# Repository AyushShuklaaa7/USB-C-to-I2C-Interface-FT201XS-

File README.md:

Overview

This project converts USB communication to I2C using the FT201XS, making it useful for testing, debugging, or interfacing with I2C-based sensors and modules.
The board is powered via USB-C and includes an onboard LDO to generate a stable 3.3V supply, which is used for both the IC and I2C communication.

## Preview

⚙️Key Components

1. FT201XS (USB to I2C Bridge)
2. TPS7A20_03 (3.3V LDO)
3. USB-C Connector
4. Power Indicator LED

🧠 Design Approach & Working

* This board is designed to provide a simple bridge between USB and I2C communication using the FT201XS IC.
* the USB D+/D- differential pairs are routed with matched lengths and kept short to ensure error-free USB Full-Speed communication.
* When the board is connected via USB-C, the 5V (VBUS) from the USB is used as the primary power source. This 5V is passed through a polyfuse for overcurrent protection and then filtered using a ferrite bead to reduce high-frequency noise. A power indicator LED is connected to VBUS to show when the board is powered.
* The 5V input is then regulated down to 3.3V using an onboard LDO. This 3.3V supply powers the FT201XS IC,The FT201XS acts as a USB-to-I2C bridge.
* It communicates with the host computer over USB and converts those signals into I2C signals (SDA and SCL), which are exposed through the output header.
* For flexibility, both 3.3V (regulated) and 5V (VBUS) are exposed on the output header. While 5V can be used to power external modules, the I2C communication itself is strictly limited to 3.3V logic levels.
* Additional protection is included using an ESD protection device on the USB data lines (D+ and D−) to safeguard the board from electrostatic discharge events.

Tools Used 
KiCad (for schematic and PCB design)

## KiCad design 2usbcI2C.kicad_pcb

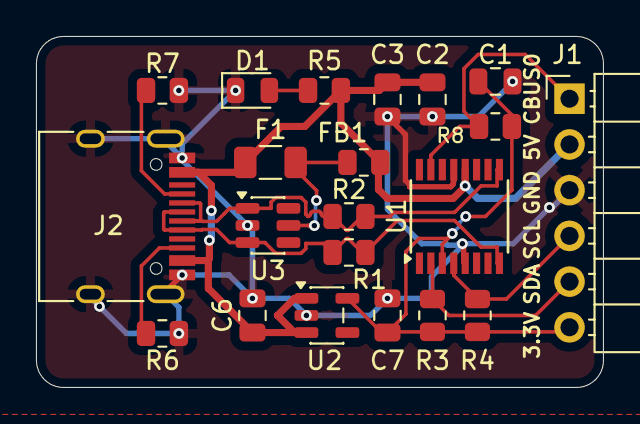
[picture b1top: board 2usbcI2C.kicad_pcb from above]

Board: 2 copper layers, 31.5 x 19.5 mm, 21 parts (0 on the bottom side), 12 nets.

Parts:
C1, C2: 100n; C_0805_2012Metric
C3: 4.7u; C_0805_2012Metric
C6, C7: 1u; C_0805_2012Metric
D1: LED; LED_0805_2012Metric
F1: Polyfuse; Fuse_1206_3216Metric
FB1: 600Ω @ 100MHz; R_0805_2012Metric
J1: Conn_01x06_MountingPin; PinHeader_1x06_P2.54mm_Horizontal
J2: USB_C_Receptacle_USB2.0_16P; USB_C_Receptacle_HRO_TYPE-C-31-M-12
R1, R2: 27; R_0805_2012Metric
R3, R4, R5, R8: 1k; R_0805_2012Metric
R6, R7: 5.1k; R_0805_2012Metric
U1: FT201XS; SSOP-16_3.9x4.9mm_P0.635mm
U2: TLV71333PDBV; SOT-23-5
U3: USBLC6-2SC6; SOT-23-6

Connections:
/CBUS0: J1.1, R8.2, U1.15 (CBUS0)
/D+: J2.A6 (D+), J2.B6 (D+), R1.1, R1.2, U1.8 (USBDP), U3.3 (I/O2)
/D-: J2.A7 (D-), J2.B7 (D-), R2.1, R2.2, U1.9 (USBDM), U3.1 (I/O1)
/SCL: J1.5, R3.2, U1.2 (SCL)
/SDA: J1.4, R4.2, U1.4 (SDA)
/VBUS: C2.1, C3.1, C6.1, F1.1, FB1.2, J1.2, J2.A4 (VBUS), J2.A9 (VBUS), J2.B4 (VBUS), J2.B9 (VBUS), R5.2, U1.12 (VCC), U2.1 (IN), U2.3 (EN)
/VCCIO: C1.1, C7.1, J1.6, R3.1, R4.1, R8.1, U1.3 (VCCIO), U2.5 (OUT)
GND: C1.2, C2.2, C3.2, C6.2, C7.2, D1.1 (K), J1.3, J2.A1 (GND), J2.A12 (GND), J2.B1 (GND), J2.B12 (GND), J2.S1 (SHIELD), R6.1, R7.2, U1.5 (GND), U1.13 (GND), U2.2 (GND), U3.2 (GND)
unnamed: D1.2 (A), R5.1
unnamed: J2.A5 (CC1), R7.1
unnamed: J2.B5 (CC2), R6.2
unnamed: F1.2, FB1.1, U3.5 (VBUS)
